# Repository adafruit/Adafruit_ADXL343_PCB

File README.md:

## Adafruit ADXL343 - Triple-Axis Accelerometer (+-2g/4g/8g/16g) w/ I2C/SPI PCB

<a href="http://www.adafruit.com/products/4097"><br/>
<a href="http://www.adafruit.com/products/4097"><br/>
Click here to purchase one from the Adafruit shop</a>

PCB files for the Adafruit ADXL343 - Triple-Axis Accelerometer (+-2g/4g/8g/16g) w/ I2C/SPI. Format is EagleCAD schematic and board layout
* https://www.adafruit.com/product/4097

### Description

Analog Devices has followed up on their popular classic, the ADXL345, with this near-drop-in-replacement, the ADXL343. Like the original, this is a triple-axis accelerometer with digital I2C and SPI interface breakout. It has a wide sensitivity range and high resolution, operating with an 10 or 13-bit internal ADC. Built-in motion detection features make tap, double-tap, activity, inactivity, and free-fall detection trivial. There's two interrupt pins, and you can map any of the interrupts independently to either of them.

The ADXL343 is nearly identical in specifications to the ADXL345, and code written for the '345 will likely work on the '343 as-is. This new accelerometer has some nice price improvements to stay within your budget.

The sensor has three axes of measurements, X Y Z, and pins that can be used either as I2C or SPI digital interfacing. You can set the sensitivity level to either +-2g, +-4g, +-8g or +-16g. The lower range gives more resolution for slow movements, the higher range is good for high speed tracking. The ADXL343 is the latest and greatest from Analog Devices, known for their exceptional quality MEMS devices.

We added an on-board 3.3V regulator and logic-level shifting circuitry, making it a perfect choice for interfacing with any 3V or 5V microcontroller or computer such as Arduino or Raspberry Pi. We've got both [Arduino (C/C++)](https://learn.adafruit.com/adxl343-breakout-learning-guide/arduino) and [CircuitPython (Python 3](https://learn.adafruit.com/adxl343-breakout-learning-guide/circuitpython)) libraries available so you can use it with any microcontroller like [Arduino, ESP8266, Metro, etc](https://learn.adafruit.com/adxl343-breakout-learning-guide/arduino) or with [Raspberry Pi or other Linux computers](https://learn.adafruit.com/adxl343-breakout-learning-guide/circuitpython) thanks to Blinka (our CircuitPython library support helper).

As if that weren't enough, we've also added SparkFun qwiic compatible STEMMA QT connectors for the I2C bus so you don't even need to solder. Just wire up to your favorite micro with a plug-and-play cable to get accelerometer data ASAP. For a no-solder experience, just wire up to your favorite micro using a STEMMA QT adapter cable. The Stemma QT connectors also mean the ADXL can be used with our various associated accessories. QT Cable is not included, but we have a variety in the shop

Each order comes with a fully tested and assembled breakout and some header for soldering to a PCB or breadboard. Comes with 9 pin 0.1" standard header in case you want to use it with a breadboard or perfboard. Two 2.5mm (0.1") mounting holes for easy attachment.You'll be up and running in under 5 minutes!

[Thanks to Digi-Key](https://www.digikey.com/) and [Analog Devices](https://www.analog.com/en/index.html) for sponsoring the development of this breakout board - we've made the PCB "[Digi-Key red](https://www.digikey.com/)" in their honor!

### License

Adafruit invests time and resources providing this open source design, please support Adafruit and open-source hardware by purchasing products from [Adafruit](https://www.adafruit.com)!

Designed by Limor Fried/Ladyada for Adafruit Industries.

Creative Commons Attribution/Share-Alike, all text above must be included in any redistribution. See license.txt for additional details.

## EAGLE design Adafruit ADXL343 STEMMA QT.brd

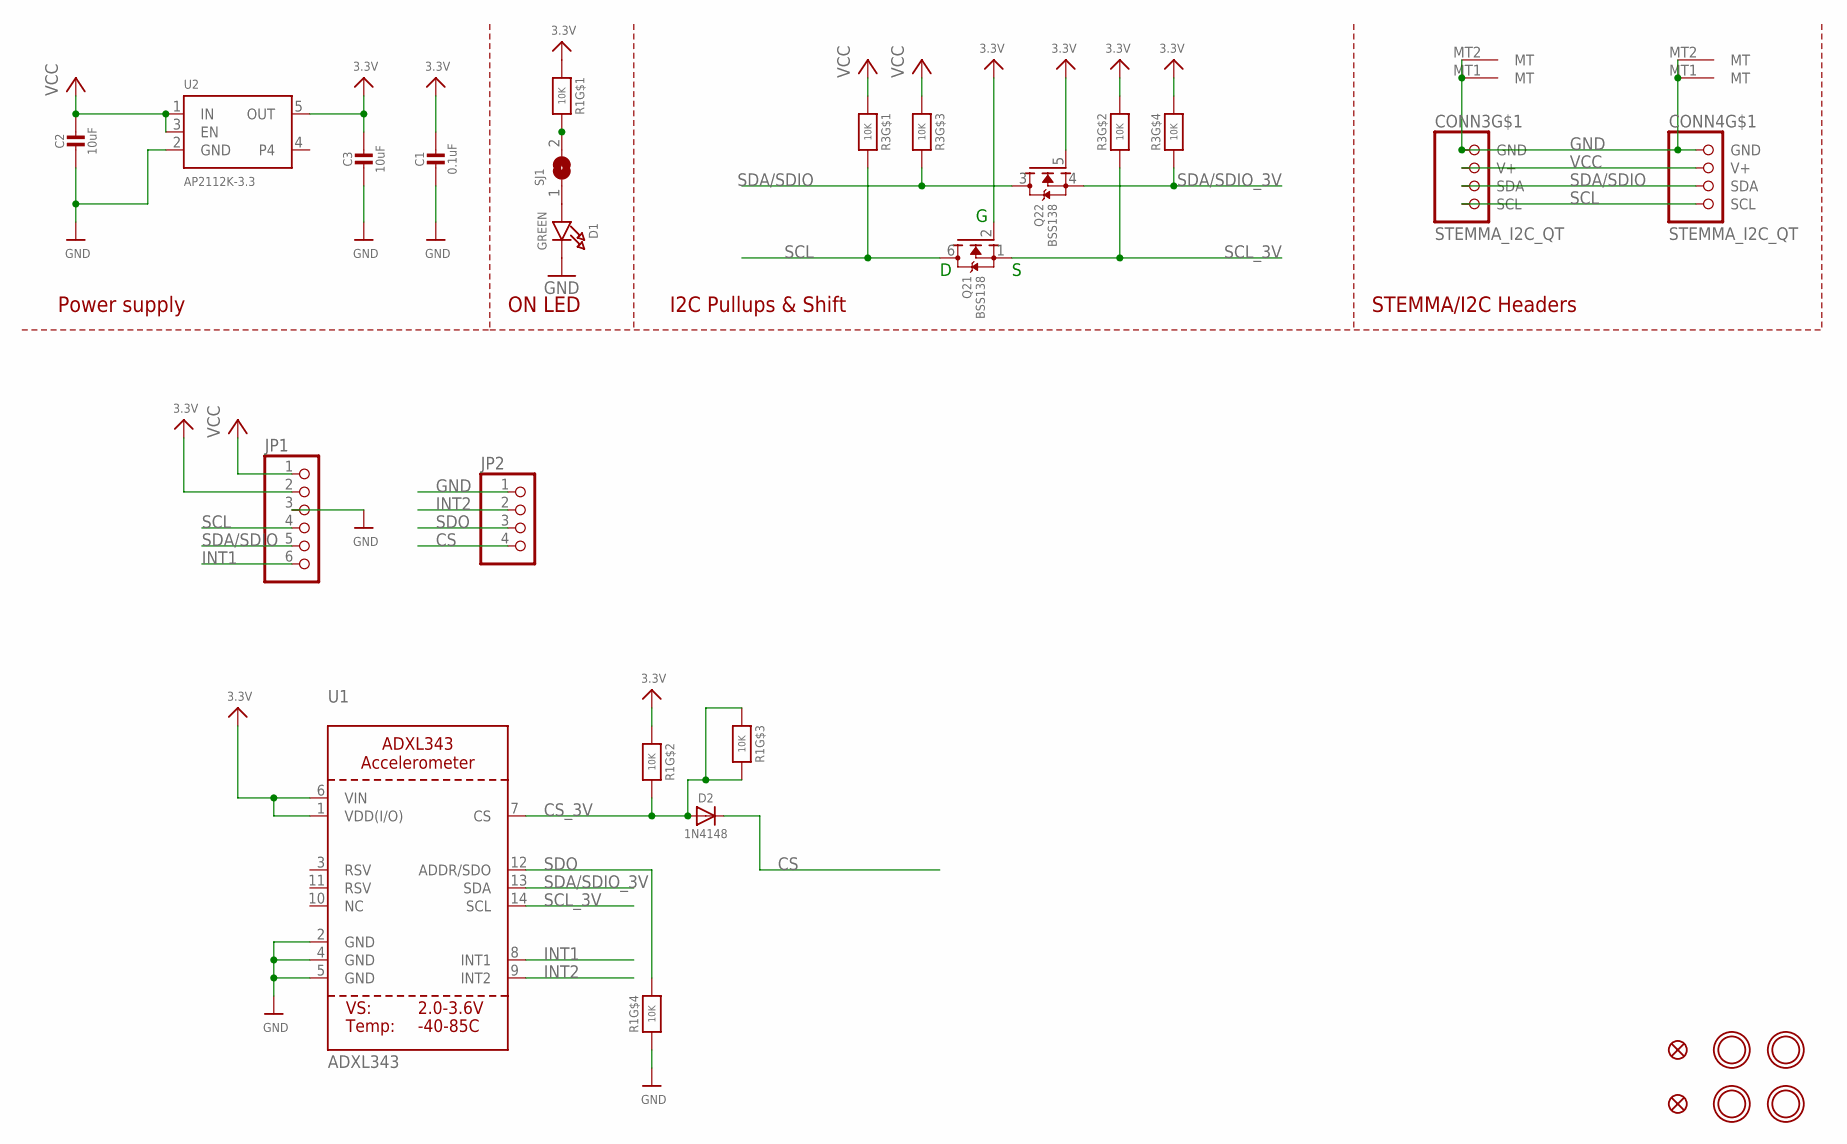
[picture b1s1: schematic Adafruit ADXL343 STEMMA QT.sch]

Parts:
C1: 0.1uF; 0603-NO
C2: 10uF; _0805MP
C3: 10uF; 0805-NO
CONN3, CONN4: STEMMA_I2C_QT; JST_SH4
D1: GREEN; CHIPLED_0603_NOOUTLINE
D2: 1N4148; SOD-323
FID3, FID4: FIDUCIAL_1MM
JP1: HEADER-1X670MIL; 1X06_ROUND_70
JP2: HEADER-1X4ROUND; 1X04_ROUND
Q2: BSS138; SOT363
R1, R3: 10K; RESPACK_4X0603
SJ1: SOLDERJUMPERCLOSED; SOLDERJUMPER_CLOSEDWIRE
U1: ADXL343; LGA14
U2: AP2112K-3.3; SOT23-5
U$1, U$17, U$19, U$21: MOUNTINGHOLE2.5; MOUNTINGHOLE_2.5_PLATED

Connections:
3.3V: C1.1, C3.1, JP1.2, Q2.2 (G), Q2.5 (G), R1.1, R1.2 (1), R3.2 (1), R3.4 (1), U1.1 (VDD(I/O)), U1.6 (VIN), U2.5 (OUT)
CS: D2.C, JP2.4
CS_3V: D2.A, R1.3 (1), R1.6 (2), R1.7 (2), U1.7 (CS)
GND: C1.2, C2.2, C3.2, CONN3.1 (GND), CONN3.MT1 (MT), CONN3.MT2 (MT), CONN4.1 (GND), CONN4.MT1 (MT), CONN4.MT2 (MT), D1.C, JP1.3, JP2.1, R1.4 (1), U1.2 (GND), U1.4 (GND), U1.5 (GND), U2.2 (GND)
INT1: JP1.6, U1.8 (INT1)
INT2: JP2.2, U1.9 (INT2)
unnamed: R1.8 (2), SJ1.2
unnamed: D1.A, SJ1.1
SCL: CONN3.4 (SCL), CONN4.4 (SCL), JP1.4, Q2.6 (D), R3.8 (2)
SCL_3V: Q2.1 (S), R3.7 (2), U1.14 (SCL)
SDA/SDIO: CONN3.3 (SDA), CONN4.3 (SDA), JP1.5, Q2.3 (D), R3.6 (2)
SDA/SDIO_3V: Q2.4 (S), R3.5 (2), U1.13 (SDA)
SDO: JP2.3, R1.5 (2), U1.12 (ADDR/SDO)
VCC: C2.1, CONN3.2 (V+), CONN4.2 (V+), JP1.1, R3.1, R3.3 (1), U2.1 (IN), U2.3 (EN)

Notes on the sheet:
I2C Pullups & Shift
STEMMA/I2C Headers
ON LED
Power supply

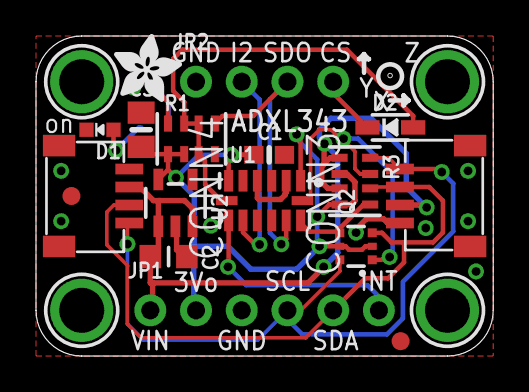
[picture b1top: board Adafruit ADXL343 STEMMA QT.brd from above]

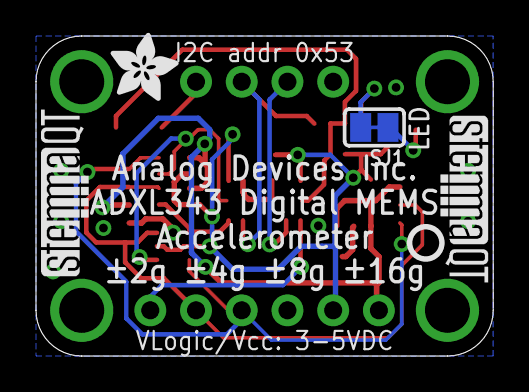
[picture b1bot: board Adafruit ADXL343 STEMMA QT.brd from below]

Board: 2 copper layers, 25.4 x 17.8 mm, 26 parts (5 on the bottom side), 14 nets.

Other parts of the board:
U$4, U$11: ADAFRUIT_3.5MM
U$25: PCBFEAT-REV-040
U$30, U$31: STEMMAQT

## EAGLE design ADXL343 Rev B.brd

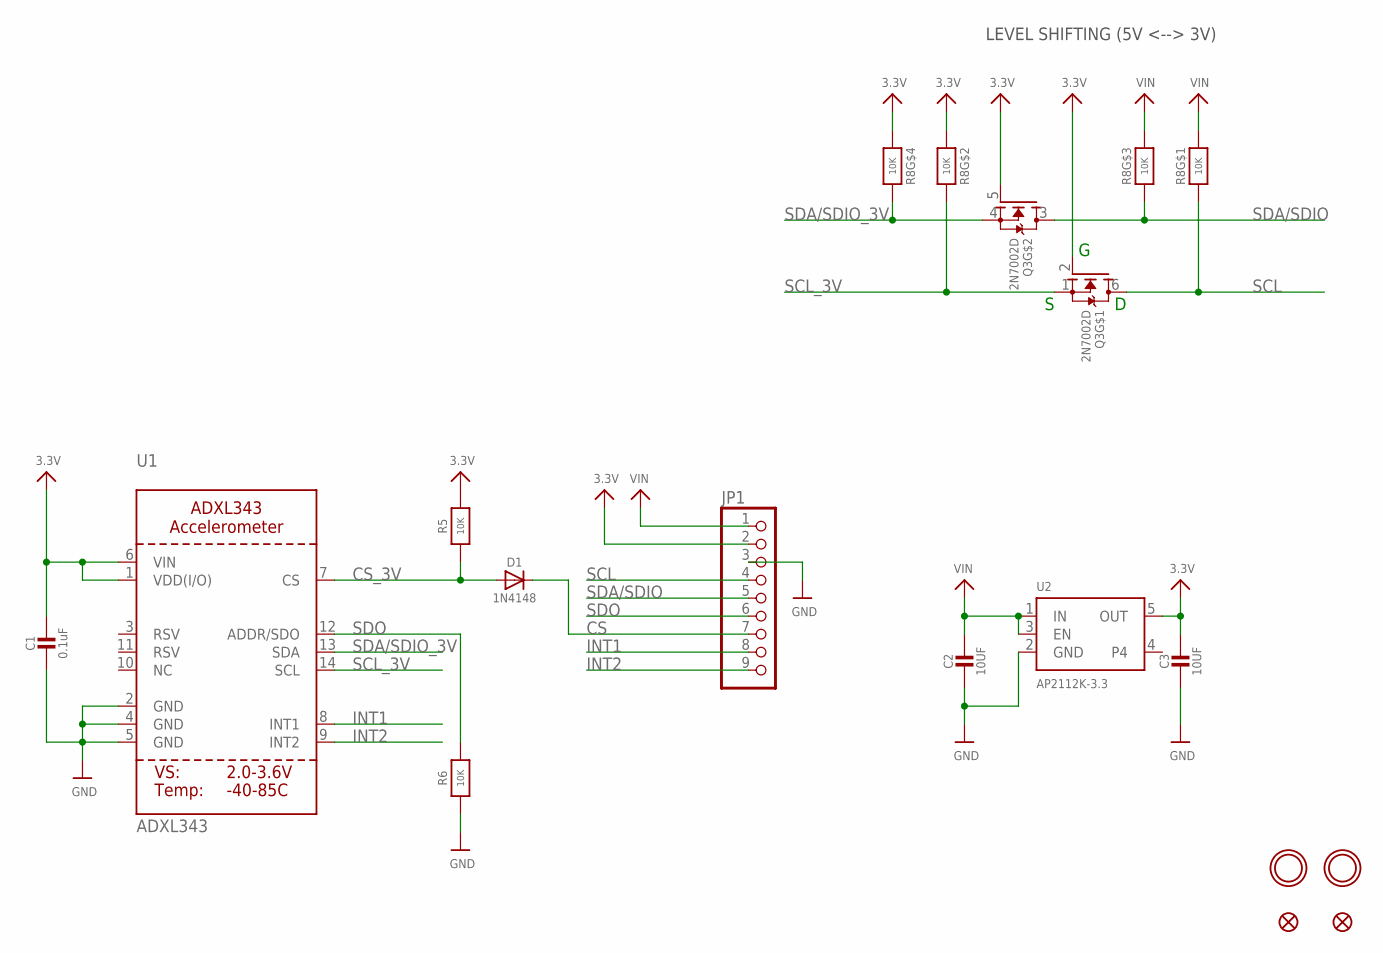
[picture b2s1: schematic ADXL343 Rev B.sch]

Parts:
C1: 0.1uF; 0603-NO
C2, C3: 10UF; 0805-NO
D1: 1N4148; SOD-323
JP1: HEADER-1X970MIL; 1X09_ROUND_70
Q3: 2N7002D; SOT363
R5, R6: 10K; 0603-NO
R8: 10K; RESPACK_4X0603
U1: ADXL343; LGA14
U2: AP2112K-3.3; SOT23-5
U$1, U$3: FIDUCIAL_1MM
U$4, U$6: MOUNTINGHOLE2.5; MOUNTINGHOLE_2.5_PLATED

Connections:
3.3V: C1.1, C3.1, JP1.2, Q3.2 (G), Q3.5 (G), R5.2, R8.2 (1), R8.4 (1), U1.1 (VDD(I/O)), U1.6 (VIN), U2.5 (OUT)
CS: D1.C, JP1.7
CS_3V: D1.A, R5.1, U1.7 (CS)
GND: C1.2, C2.2, C3.2, JP1.3, R6.1, U1.2 (GND), U1.4 (GND), U1.5 (GND), U2.2 (GND)
INT1: JP1.8, U1.8 (INT1)
INT2: JP1.9, U1.9 (INT2)
SCL: JP1.4, Q3.6 (D), R8.8 (2)
SCL_3V: Q3.1 (S), R8.7 (2), U1.14 (SCL)
SDA/SDIO: JP1.5, Q3.3 (D), R8.6 (2)
SDA/SDIO_3V: Q3.4 (S), R8.5 (2), U1.13 (SDA)
SDO: JP1.6, R6.2, U1.12 (ADDR/SDO)
VIN: C2.1, JP1.1, R8.1, R8.3 (1), U2.1 (IN), U2.3 (EN)

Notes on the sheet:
LEVEL SHIFTING (5V <--> 3V)

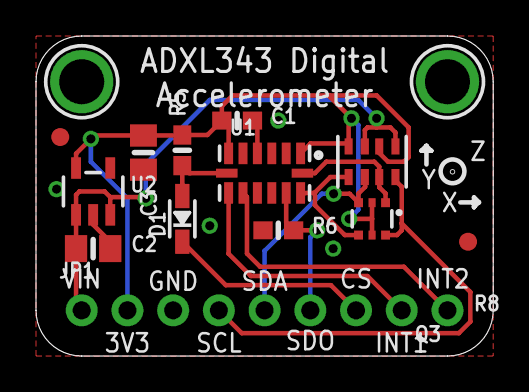
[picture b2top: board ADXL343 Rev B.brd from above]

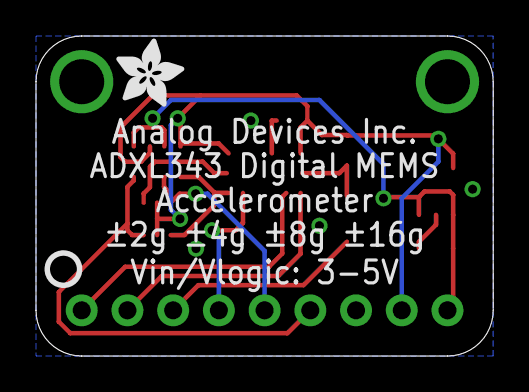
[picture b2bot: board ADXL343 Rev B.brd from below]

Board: 2 copper layers, 25.4 x 17.8 mm, 17 parts (2 on the bottom side), 12 nets.

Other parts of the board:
U$5: ADAFRUIT_3.5MM
U$7: PCBFEAT-REV-040

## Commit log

2019-07-17 updated to use cookiecutter for pcb repos
2022-03-22 Updating STEMMA

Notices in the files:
parts and their libraries:
microbuilder: This work is placed in the public domain, and may be freely used for commercial and non-commercial work with the following conditions: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
